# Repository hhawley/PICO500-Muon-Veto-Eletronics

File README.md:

This github contains three projects all related to the Muon Veto electronics:

## LED driver
The LED driver is meant to drive 2 LEDs (for redundancy) in ultra short pulses (10-100 ns). These are used to verify the PMTs are working. These boards are 99%
finished. The final design needs 12 of these.

## Fan-in-Fan-out
This is meant to be located inside the crate for the LEDs. Only 1 is required.
It is intentionally incomplete as the final implementation does not really care
about how this board is constructed but it MUST follow the circuit shown.

## Nhit counting board
A 2-3 slot VME board. This one has two projects:

### Nhit comparators
The comparators used to digitize the PMTs output and fed into the counting board. The output is mean to be a SYGYZY port that connects to the FPGA. This needs to be finished.

### Nhit counting Board
Based on a Eclypse Z7, the code here is just a small sample of the Verilog code
used for the final design. The entire project I used to originally program the board is not found here because it is too big and usually does not port well.

Read me thesis or ask me a question!

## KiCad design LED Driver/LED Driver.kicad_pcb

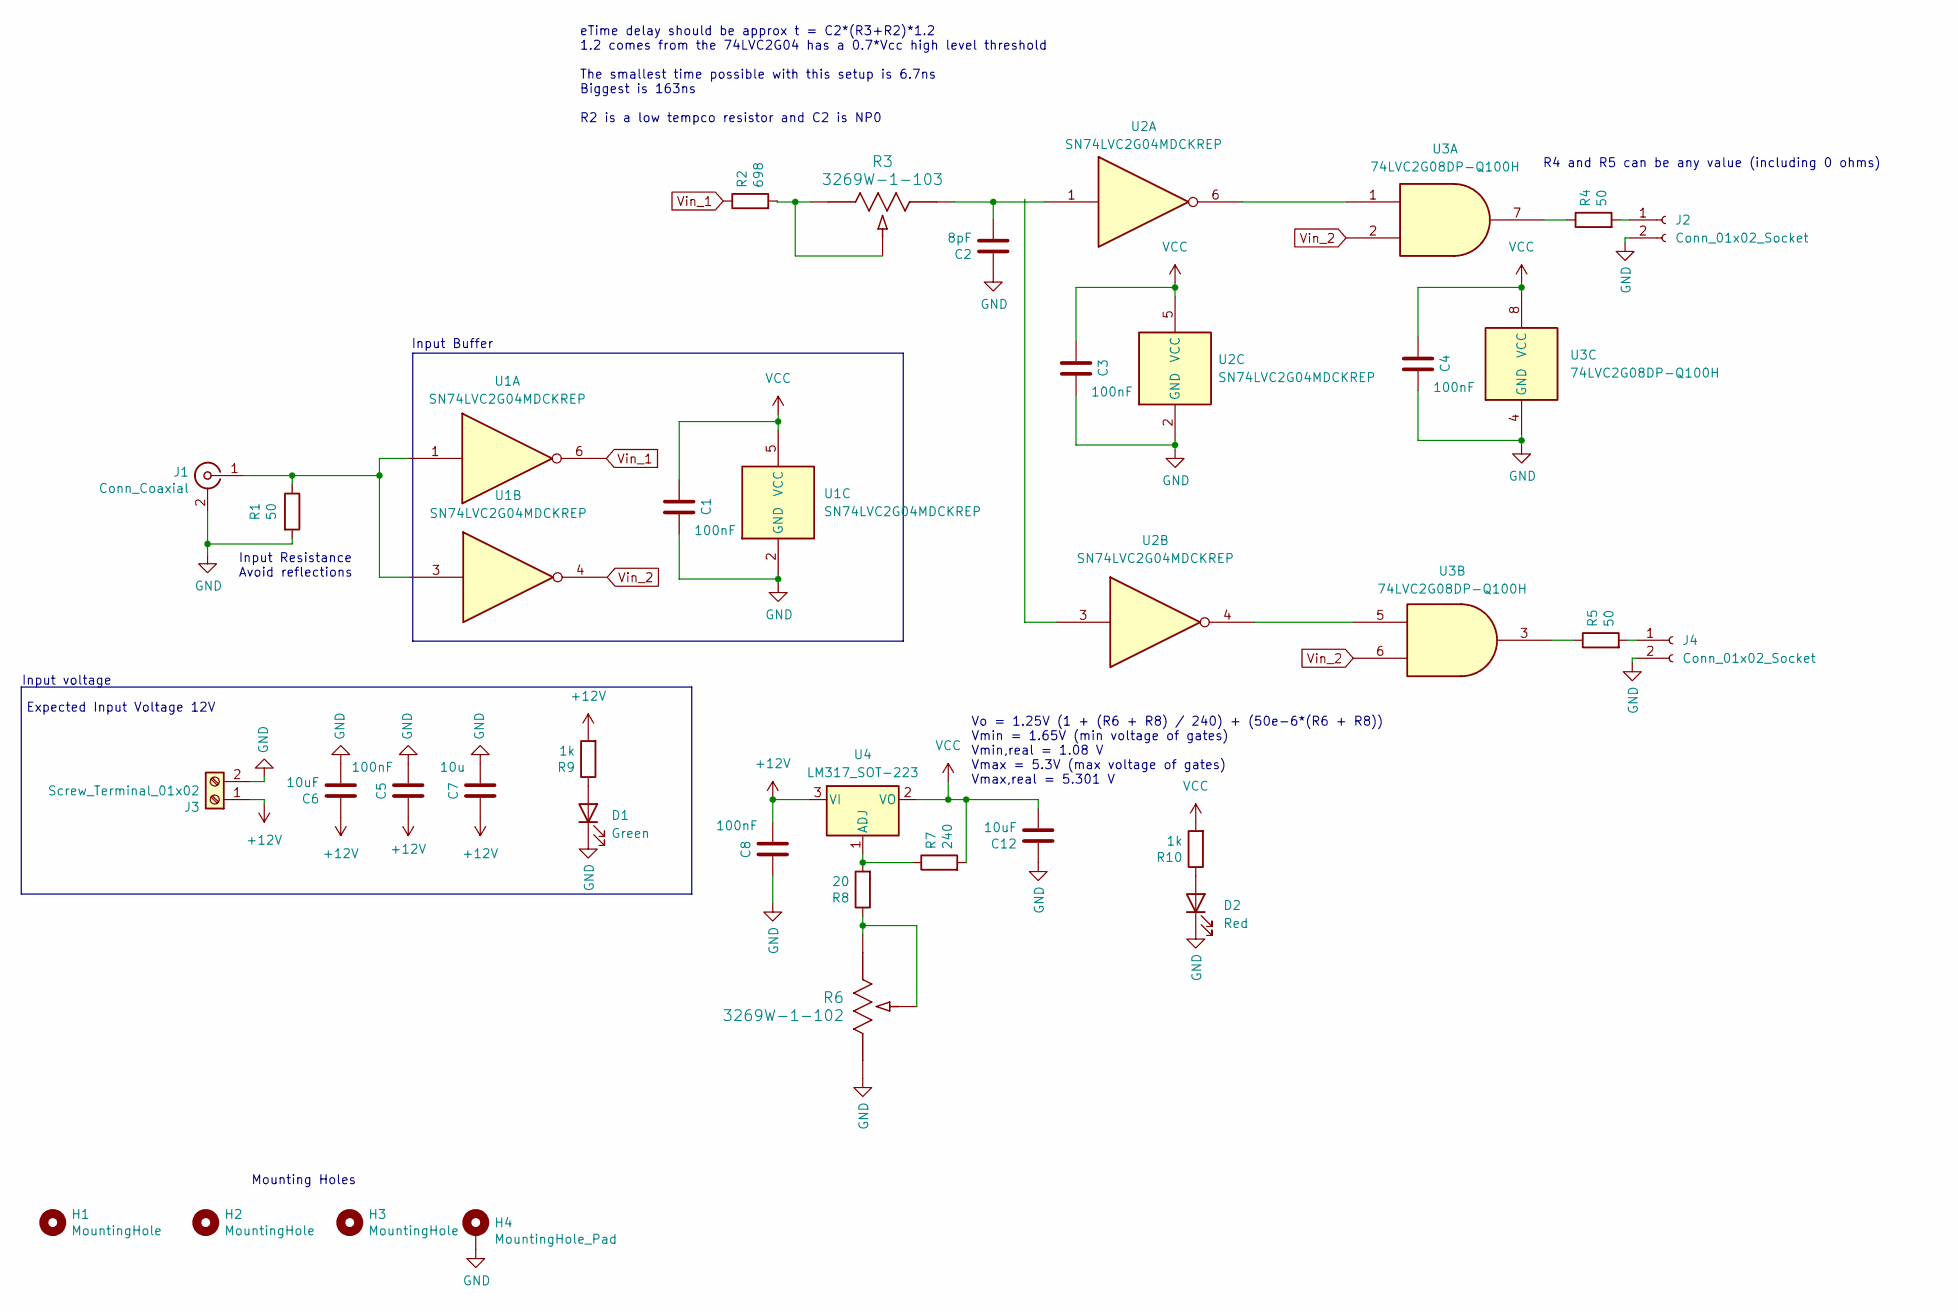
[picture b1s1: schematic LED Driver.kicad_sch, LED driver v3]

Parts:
C1, C3, C4, C5, C8: 100nF; C_0603_1608Metric_Pad1.08x0.95mm_HandSolder
C2: 8pF; C_0603_1608Metric_Pad1.08x0.95mm_HandSolder
C6, C12: 10uF; C_0805_2012Metric_Pad1.18x1.45mm_HandSolder
C7: 10u; CP_Radial_D6.3mm_P2.50mm
D1: Green; LED_0805_2012Metric_Pad1.15x1.40mm_HandSolder
D2: Red; LED_0805_2012Metric_Pad1.15x1.40mm_HandSolder
H1, H2, H3: MountingHole; MountingHole_3.2mm_M3
H4: MountingHole_Pad; MountingHole_3.2mm_M3_DIN965_Pad
J1: Conn_Coaxial; SMA_Amphenol_901-144_Vertical
J2, J4: Conn_01x02_Socket; LED_D5.0mm_Horizontal_O3.81mm_Z9.0mm
J3: Screw_Terminal_01x02; TerminalBlock_bornier-2_P5.08mm
R1: 50; C_1206_3216Metric_Pad1.33x1.80mm_HandSolder
R2: 698; R_0603_1608Metric_Pad0.98x0.95mm_HandSolder; Mfr. # RP73PF1J698RBTDF
R3: 3269W-1-103; Potentiometer_Bourns_3269W_Vertical
R4, R5: 50; R_0603_1608Metric_Pad0.98x0.95mm_HandSolder
R6: 3269W-1-102; Potentiometer_Bourns_3269W_Vertical
R7: 240; R_0603_1608Metric_Pad0.98x0.95mm_HandSolder
R8: 20; R_0603_1608Metric_Pad0.98x0.95mm_HandSolder
R9, R10: 1k; R_0603_1608Metric_Pad0.98x0.95mm_HandSolder
U1, U2: SN74LVC2G04MDCKREP; SOT-363_SC-70-6
U3: 74LVC2G08DP-Q100H; TSSOP-8_3x3mm_P0.65mm
U4: LM317_SOT-223; SOT-223-3_TabPin2

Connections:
+12V: C5.1, C6.1, C7.1, C8.2, J3.1, R9.2, U4.3 (VI)
GND: C1.2, C2.1, C3.2, C4.2, C5.2, C6.2, C7.2, C8.1, C12.1, D1.1 (K), D2.1 (K), H4.1, J1.2 (Ext), J2.2, J3.2, J4.2, R1.2, R6.3, U1.2 (GND), U2.2 (GND), U3.4 (GND)
unnamed: C2.2, R3.1, U2.1
unnamed: D1.2 (A), R9.1
unnamed: D2.2 (A), R10.1
unnamed: J1.1 (In), R1.1, U1.1, U1.3
unnamed: J2.1, R4.2
unnamed: J4.1, R5.2
unnamed: R2.2, R3.2, R3.3
unnamed: R4.1, U3.7
unnamed: R5.1, U3.3
unnamed: R6.1, R6.2, R8.1
unnamed: U2.4, U3.5
unnamed: U2.6, U3.1
unnamed: R7.1, R8.2, U4.1 (ADJ)
VCC: C1.1, C3.1, C4.1, C12.2, R7.2, R10.2, U1.5 (VCC), U2.5 (VCC), U3.8 (VCC), U4.2 (VO)
Vin_1: R2.1, U1.6
Vin_2: U1.4, U3.2, U3.6

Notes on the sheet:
eTime delay should be approx t = C2*(R3+R2)*1.2 1.2 comes from the 74LVC2G04 has a 0.7*Vcc high level threshold The smallest time possible with this setup is 6.7ns Biggest is 163ns R2 is a low tempco resistor and C2 is NP0
Input Buffer
Input Resistance Avoid reflections
Vo = 1.25V (1 + (R6 + R8) / 240) + (50e-6*(R6 + R8)) Vmin = 1.65V (min voltage of gates) Vmin,real = 1.08 V Vmax = 5.3V (max voltage of gates) Vmax,real = 5.301 V
Mounting Holes
Input voltage
Expected Input Voltage 12V
R4 and R5 can be any value (including 0 ohms)

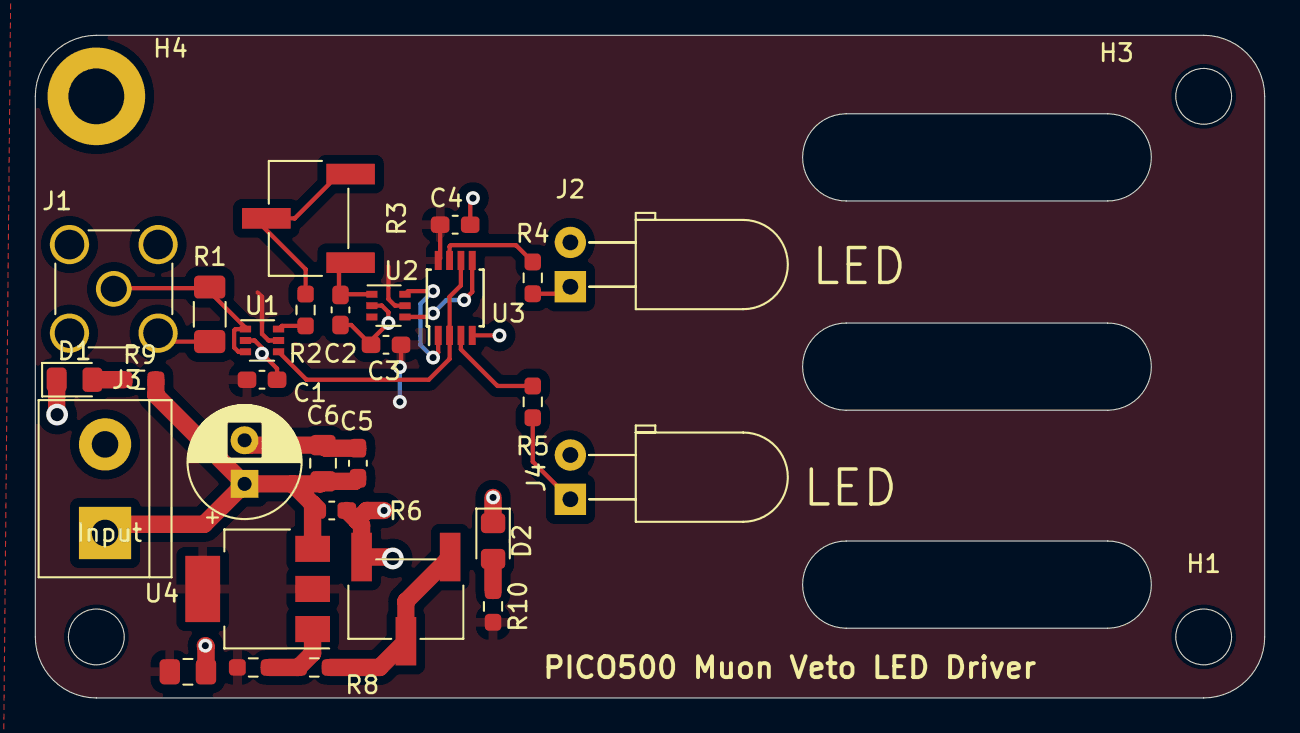
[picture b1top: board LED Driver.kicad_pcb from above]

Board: 2 copper layers, 70.5 x 38.0 mm, 33 parts (0 on the bottom side), 18 nets.

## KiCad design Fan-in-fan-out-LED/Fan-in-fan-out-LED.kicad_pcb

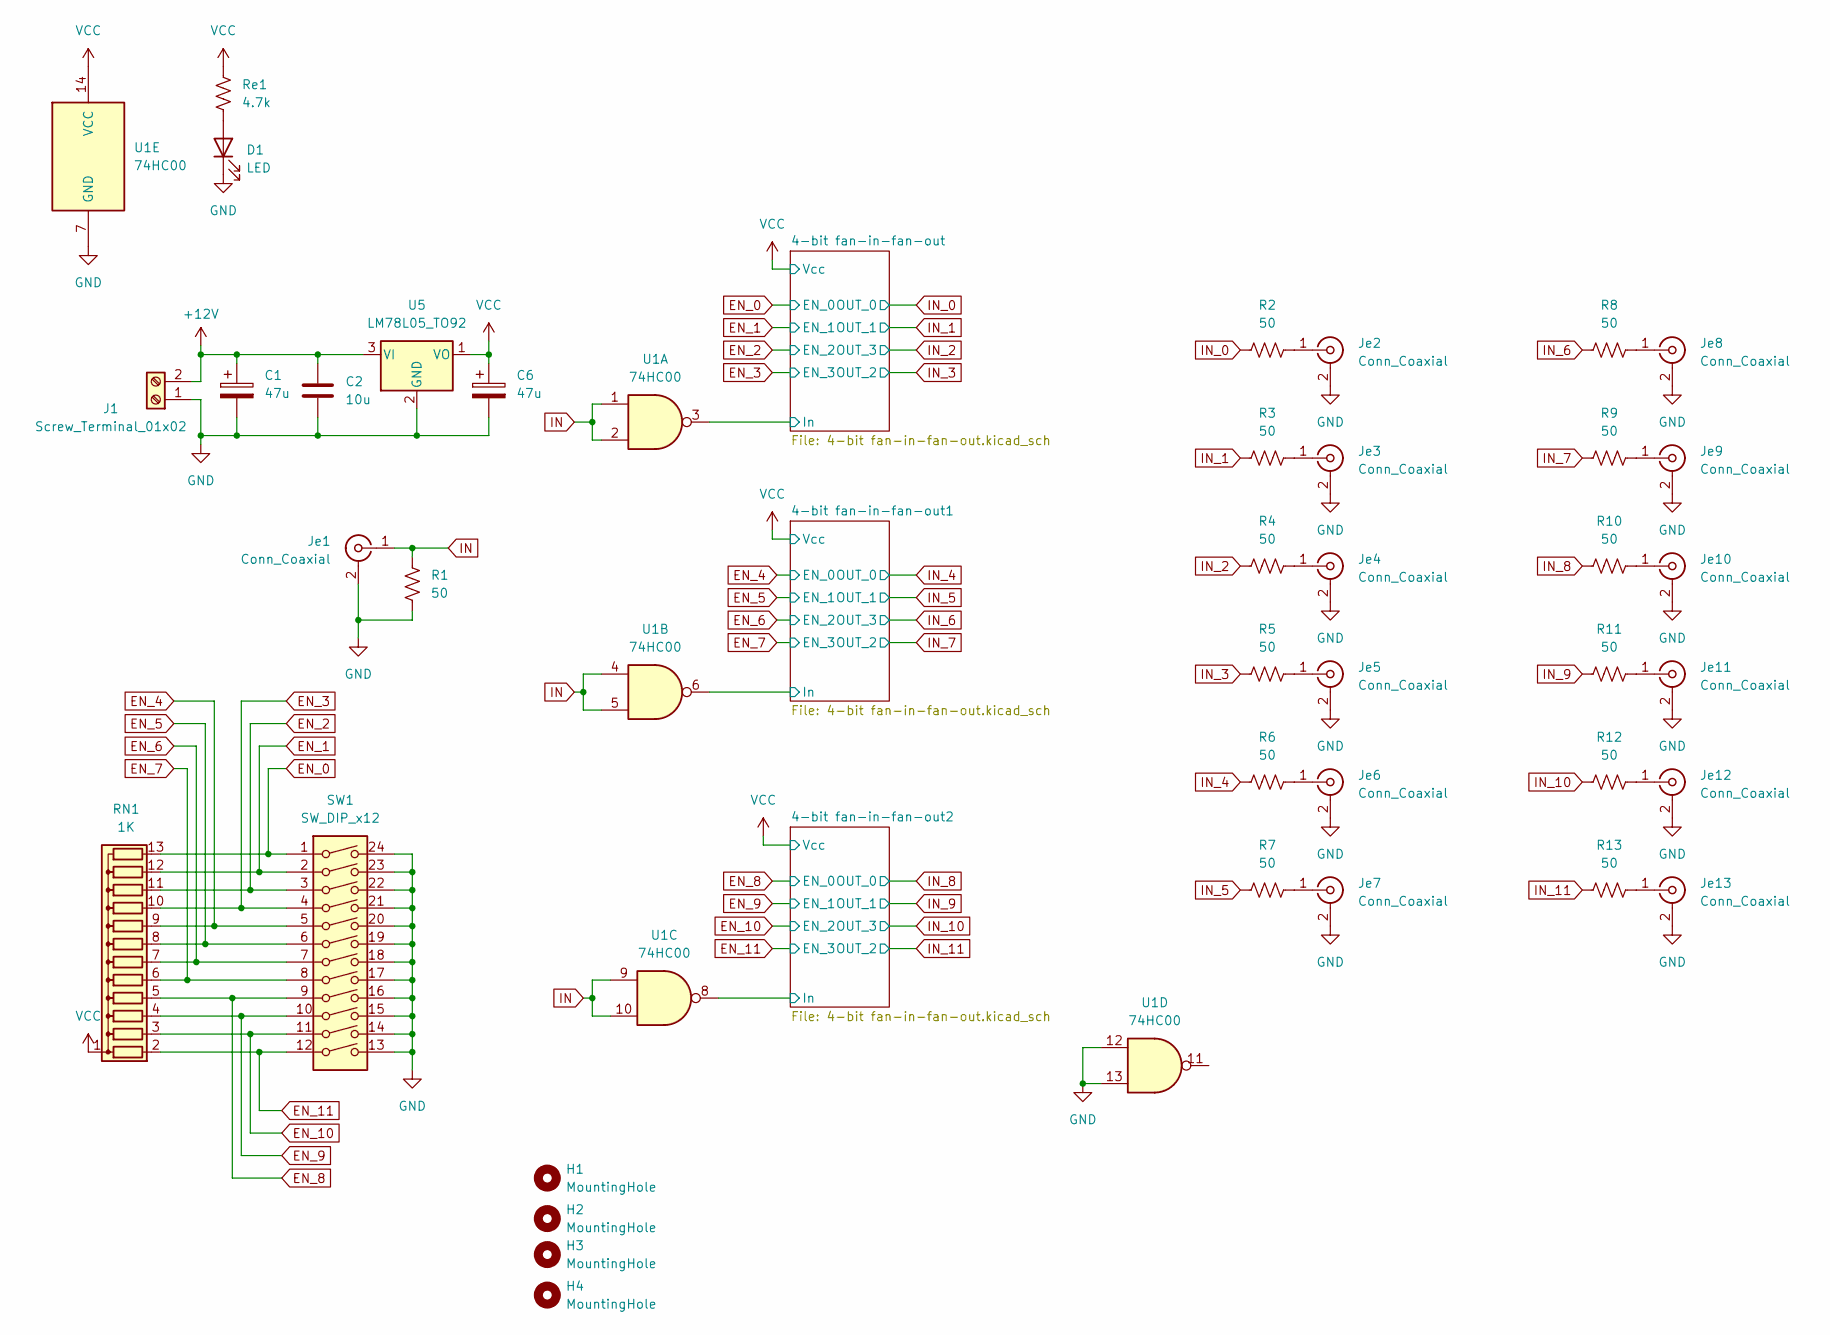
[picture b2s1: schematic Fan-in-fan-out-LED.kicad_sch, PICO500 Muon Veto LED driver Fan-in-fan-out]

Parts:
C1, C6: 47u; CP_Radial_D10.0mm_P5.00mm
C2: 10u; C_1206_3216Metric_Pad1.33x1.80mm_HandSolder
D1: LED; LED_D5.0mm_IRGrey
H1, H2, H3, H4: MountingHole; MountingHole_3.2mm_M3_ISO7380
J1: Screw_Terminal_01x02; TerminalBlock_TE_282834-2_1x02_P2.54mm_Horizontal
Je1, Je2, Je3, Je4, Je5, Je6, Je7, Je8, Je9, Je10, Je11, Je12, Je13: Conn_Coaxial; SMA_Amphenol_901-143_Horizontal
R1, R2, R3, R4, R5, R6, R7, R8, R9, R10, R11, R12, R13: 50; R_1206_3216Metric_Pad1.30x1.75mm_HandSolder
RN1: 1K; R_Array_SIP13
Re1: 4.7k; R_1206_3216Metric_Pad1.30x1.75mm_HandSolder
SW1: SW_DIP_x12; SW_DIP_SPSTx12_Slide_9.78x32.66mm_W7.62mm_P2.54mm
U1: 74HC00; DIP-14_W7.62mm_LongPads
U5: LM78L05_TO92; TO-92_Inline

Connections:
+12V: C1.1, C2.1, J1.2, U5.3 (VI)
/4-bit fan-in-fan-out1/In: U1.6; also elsewhere on the board
/4-bit fan-in-fan-out2/In: U1.8; also elsewhere on the board
/4-bit fan-in-fan-out/In: U1.3; also elsewhere on the board
EN_0: RN1.13 (R12), SW1.1; also elsewhere on the board
EN_1: RN1.12 (R11), SW1.2; also elsewhere on the board
EN_2: RN1.11 (R10), SW1.3; also elsewhere on the board
EN_3: RN1.10 (R9), SW1.4; also elsewhere on the board
EN_4: RN1.9 (R8), SW1.5; also elsewhere on the board
EN_5: RN1.8 (R7), SW1.6; also elsewhere on the board
EN_6: RN1.7 (R6), SW1.7; also elsewhere on the board
EN_7: RN1.6 (R5), SW1.8; also elsewhere on the board
EN_8: RN1.5 (R4), SW1.9; also elsewhere on the board
EN_9: RN1.4 (R3), SW1.10; also elsewhere on the board
EN_10: RN1.3 (R2), SW1.11; also elsewhere on the board
EN_11: RN1.2 (R1), SW1.12; also elsewhere on the board
GND: C1.2, C2.2, C6.2, D1.1 (K), J1.1, Je1.2 (Ext), Je2.2 (Ext), Je3.2 (Ext), Je4.2 (Ext), Je5.2 (Ext), Je6.2 (Ext), Je7.2 (Ext), Je8.2 (Ext), Je9.2 (Ext), Je10.2 (Ext), Je11.2 (Ext), Je12.2 (Ext), Je13.2 (Ext), R1.1, SW1.13, SW1.14, SW1.15, SW1.16, SW1.17, SW1.18, SW1.19, SW1.20, SW1.21, SW1.22, SW1.23, SW1.24, U1.7 (GND), U1.12, U1.13, U5.2 (GND); also elsewhere on the board
IN: Je1.1 (In), R1.2, U1.1, U1.2, U1.4, U1.5, U1.9, U1.10
IN_0: R2.1; also elsewhere on the board
IN_1: R3.1; also elsewhere on the board
IN_2: R4.1; also elsewhere on the board
IN_3: R5.1; also elsewhere on the board
IN_4: R6.1; also elsewhere on the board
IN_5: R7.1; also elsewhere on the board
IN_6: R8.1; also elsewhere on the board
IN_7: R9.1; also elsewhere on the board
IN_8: R10.1; also elsewhere on the board
IN_9: R11.1; also elsewhere on the board
IN_10: R12.1; also elsewhere on the board
IN_11: R13.1; also elsewhere on the board
unnamed: D1.2 (A), Re1.1
unnamed: Je2.1 (In), R2.2
unnamed: Je3.1 (In), R3.2
unnamed: Je4.1 (In), R4.2
unnamed: Je5.1 (In), R5.2
unnamed: Je6.1 (In), R6.2
unnamed: Je7.1 (In), R7.2
unnamed: Je8.1 (In), R8.2
unnamed: Je9.1 (In), R9.2
unnamed: Je10.1 (In), R10.2
unnamed: Je11.1 (In), R11.2
unnamed: Je12.1 (In), R12.2
unnamed: Je13.1 (In), R13.2
VCC: C6.1, RN1.1 (common), Re1.2, U1.14 (VCC), U5.1 (VO); also elsewhere on the board

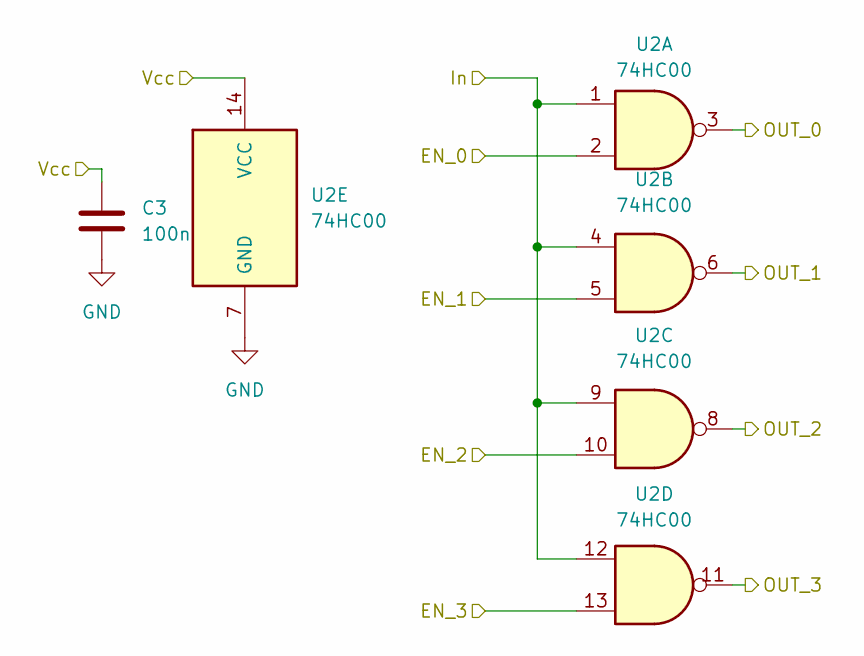
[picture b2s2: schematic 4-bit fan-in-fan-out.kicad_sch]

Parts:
C3: 100n; C_0805_2012Metric_Pad1.18x1.45mm_HandSolder
U2: 74HC00; DIP-14_W7.62mm_LongPads

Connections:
/4-bit fan-in-fan-out/In: U2.1, U2.4, U2.9, U2.12; also elsewhere on the board
EN_0: U2.2; also elsewhere on the board
EN_1: U2.5; also elsewhere on the board
EN_2: U2.10; also elsewhere on the board
EN_3: U2.13; also elsewhere on the board
GND: C3.2, U2.7 (GND); also elsewhere on the board
IN_0: U2.3; also elsewhere on the board
IN_1: U2.6; also elsewhere on the board
IN_2: U2.11; also elsewhere on the board
IN_3: U2.8; also elsewhere on the board
VCC: C3.1, U2.14 (VCC); also elsewhere on the board

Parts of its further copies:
C4, C5: 100n; C_0805_2012Metric_Pad1.18x1.45mm_HandSolder
U3, U4: 74HC00; DIP-14_W7.62mm_LongPads

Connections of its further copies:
/4-bit fan-in-fan-out1/In: U3.1, U3.4, U3.9, U3.12; also elsewhere on the board
/4-bit fan-in-fan-out2/In: U4.1, U4.4, U4.9, U4.12; also elsewhere on the board
EN_4: U3.2; also elsewhere on the board
EN_5: U3.5; also elsewhere on the board
EN_6: U3.10; also elsewhere on the board
EN_7: U3.13; also elsewhere on the board
EN_8: U4.2; also elsewhere on the board
EN_9: U4.5; also elsewhere on the board
EN_10: U4.10; also elsewhere on the board
EN_11: U4.13; also elsewhere on the board
GND: C4.2, C5.2, U3.7 (GND), U4.7 (GND); also elsewhere on the board
IN_4: U3.3; also elsewhere on the board
IN_5: U3.6; also elsewhere on the board
IN_6: U3.11; also elsewhere on the board
IN_7: U3.8; also elsewhere on the board
IN_8: U4.3; also elsewhere on the board
IN_9: U4.6; also elsewhere on the board
IN_10: U4.11; also elsewhere on the board
IN_11: U4.8; also elsewhere on the board
VCC: C4.1, C5.1, U3.14 (VCC), U4.14 (VCC); also elsewhere on the board

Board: 2 copper layers, 46 parts (0 on the bottom side), 44 nets, no tracks yet.

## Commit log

2024-02-17 First commit!
2024-05-09 Added more comments to LED driver
2024-07-06 Fixed an issue with a connection of one of the LED outputs.
